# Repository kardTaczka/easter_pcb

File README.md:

# Easter PCB

## Quick view of PCB

Below are presented screenshots of 3d render PCB and schematic.

### 1. Front

### 2. Back

### 3. Schematic

---

## About
**Dual-Channel Alternating Output** -  The NE555 timer operates at approximately 0.2 Hz. Its square wave output is smoothed by an RC integration network consisting of a 10 kΩ resistor and a 50 µF capacitor bank (achieved by placing five 10 µF MLCCs in parallel). This analog signal drives a complementary transistor pair consisting of a BCP56 (NPN) and a BCP53 (PNP). 

Instead of driving a single array, the load is split into two separate LED rails. Because the NPN and PNP transistors conduct on opposite voltage swings, they create an alternating "breathing" effect. When the capacitor charges, the NPN rail fades in while the PNP rail fades out. When the voltage drops, the cycle reverses. The peak forward current is hardware-limited to a safe and visually pleasing 3 mA per LED.

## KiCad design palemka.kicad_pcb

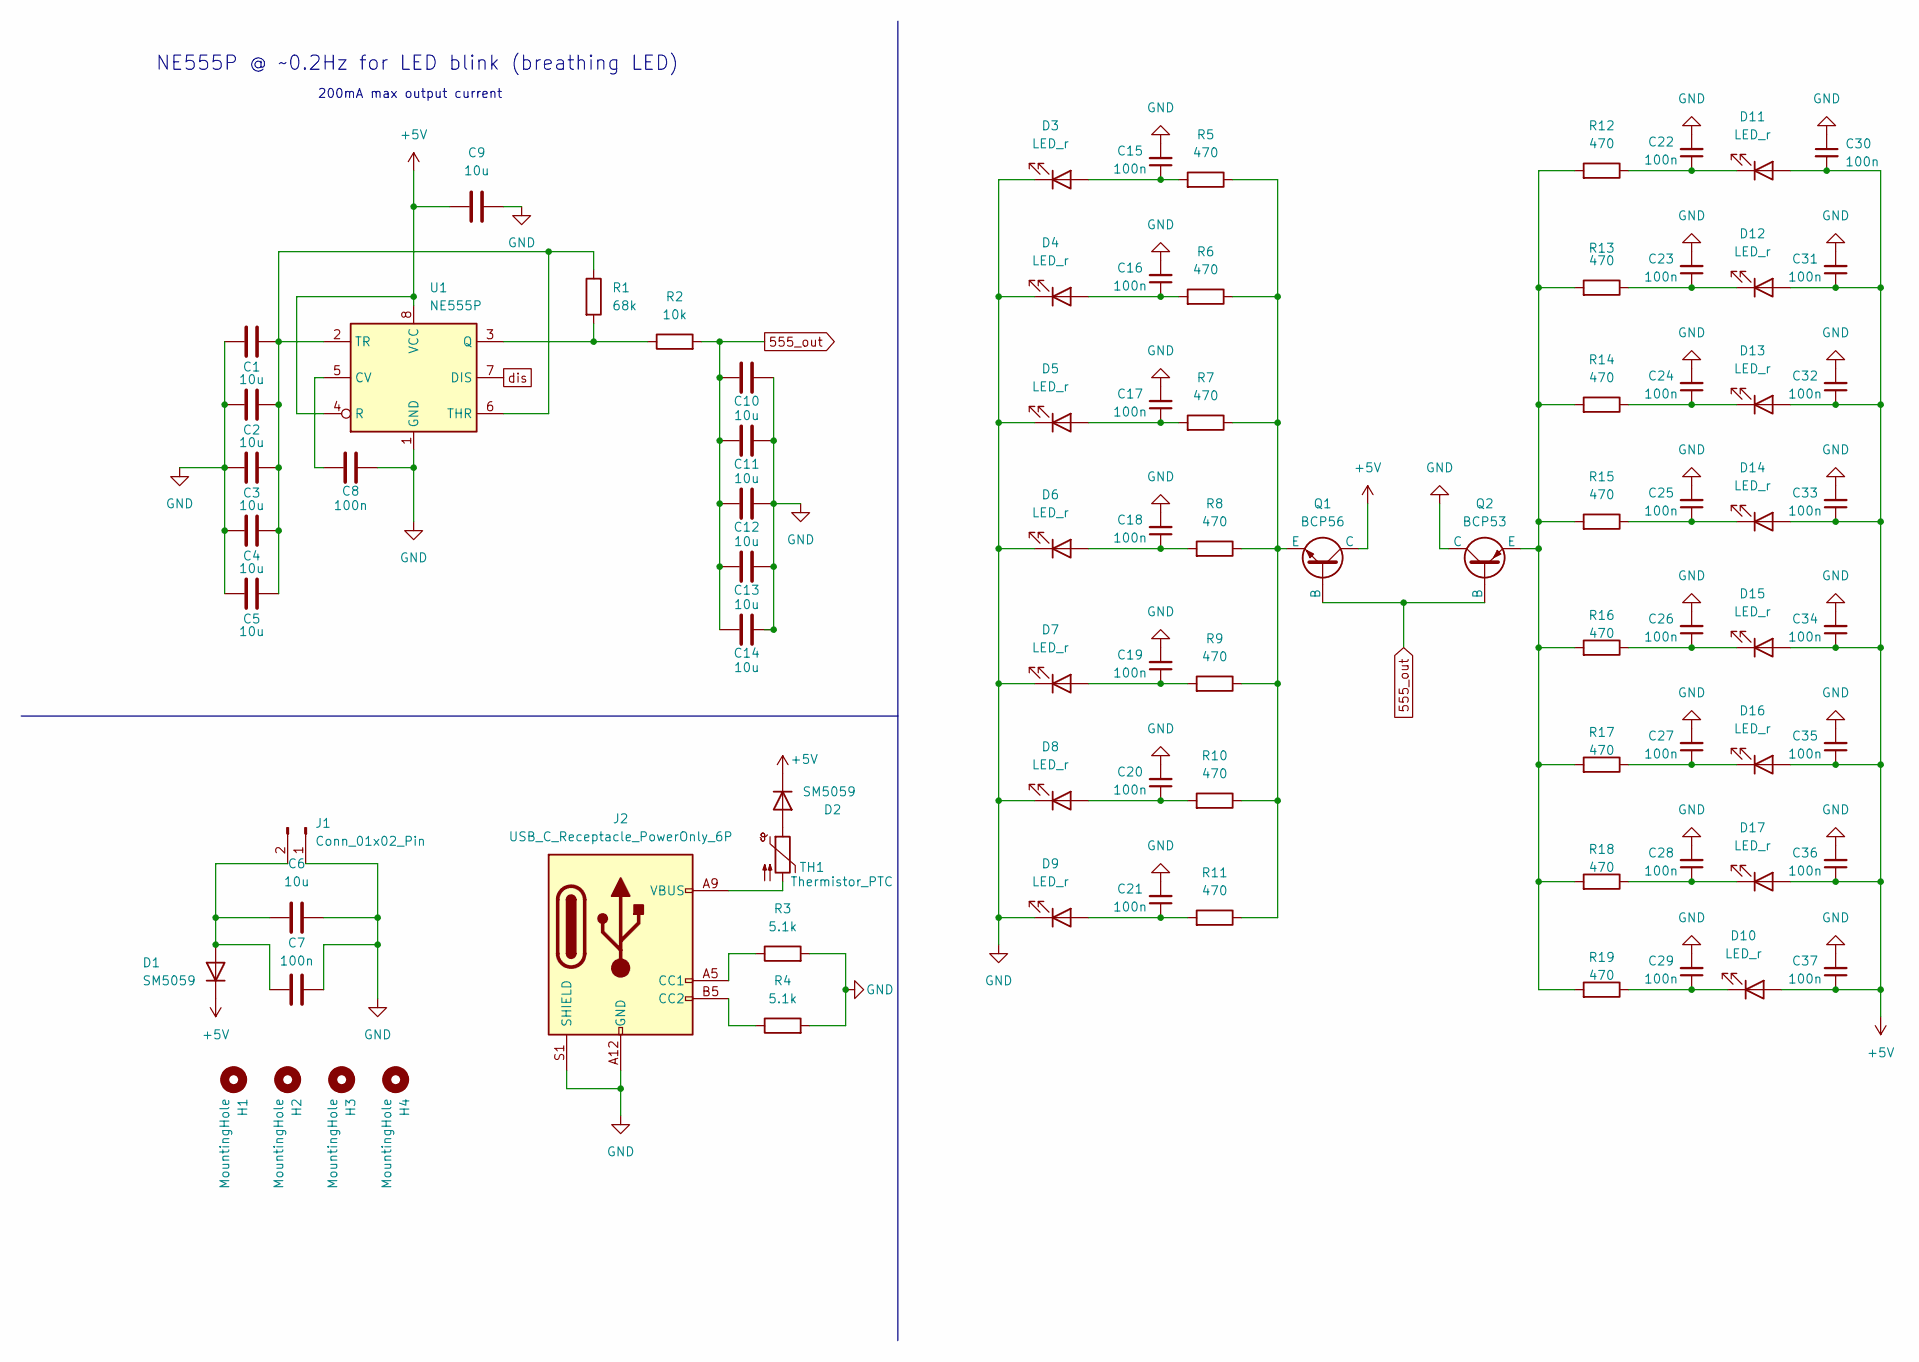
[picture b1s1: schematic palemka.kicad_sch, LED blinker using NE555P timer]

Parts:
C1, C2, C3, C4, C5, C6, C9, C10, C11, C12, C13, C14: 10u; C_0805_2012Metric_Pad1.18x1.45mm_HandSolder
C7, C8, C15, C16, C17, C18, C19, C20, C21, C22, C23, C24, C25, C26, C27, C28, C29, C30, C31, C32, C33, C34, C35, C36, C37: 100n; C_0805_2012Metric_Pad1.18x1.45mm_HandSolder
D1, D2: SM5059; D_SMA
D3, D4, D5, D6, D7, D8, D9, D10, D11, D12, D13, D14, D15, D16, D17: LED_r; LED_0805_2012Metric_Pad1.15x1.40mm_HandSolder
H1, H2, H3, H4: MountingHole; MountingHole_3.2mm_M3
J1: Conn_01x02_Pin; PinHeader_1x02_P2.54mm_Vertical
J2: USB_C_Receptacle_PowerOnly_6P; usb4970
Q1: BCP56; SOT-223
Q2: BCP53; SOT-223
R1: 68k; R_0805_2012Metric_Pad1.20x1.40mm_HandSolder
R2: 10k; R_0805_2012Metric_Pad1.20x1.40mm_HandSolder
R3, R4: 5.1k; R_0805_2012Metric_Pad1.20x1.40mm_HandSolder
R5, R6, R7, R8, R9, R10, R11, R12, R13, R14, R15, R16, R17, R18, R19: 470; R_0805_2012Metric_Pad1.20x1.40mm_HandSolder
TH1: Thermistor_PTC; R_1206_3216Metric_Pad1.30x1.75mm_HandSolder
U1: NE555P; SOIC-8_3.9x4.9mm_P1.27mm

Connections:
555_out: C10.1, C11.1, C12.1, C13.1, C14.1, Q1.2 (B), Q2.2 (B), R2.2
+5V: C9.1, C30.2, C31.1, C32.1, C33.1, C34.1, C35.1, C36.1, C37.1, D1.1 (K), D2.1 (K), D10.2 (A), D11.2 (A), D12.2 (A), D13.2 (A), D14.2 (A), D15.2 (A), D16.2 (A), D17.2 (A), Q1.1 (C), U1.4 (R), U1.8 (VCC)
GND: C1.2, C2.2, C3.2, C4.2, C5.2, C6.2, C7.1, C8.2, C9.2, C10.2, C11.2, C12.2, C13.2, C14.2, C15.2, C16.2, C17.2, C18.2, C19.2, C20.2, C21.2, C22.2, C23.2, C24.2, C25.2, C26.2, C27.2, C28.2, C29.2, C30.1, C31.2, C32.2, C33.2, C34.2, C35.2, C36.2, C37.2, D3.1 (K), D4.1 (K), D5.1 (K), D6.1 (K), D7.1 (K), D8.1 (K), D9.1 (K), J1.1, J2.A12 (GND), J2.B12 (GND), J2.S1 (SHIELD), Q2.1 (C), R3.2, R4.2, U1.1 (GND)
unnamed: C6.1, C7.2, D1.2 (A), J1.2
unnamed: D2.2 (A), TH1.1
unnamed: C15.1, D3.2 (A), R5.2
unnamed: C16.1, D4.2 (A), R6.2
unnamed: C17.1, D5.2 (A), R7.2
unnamed: C18.1, D6.2 (A), R8.2
unnamed: C19.1, D7.2 (A), R9.2
unnamed: C20.1, D8.2 (A), R10.2
unnamed: C21.1, D9.2 (A), R11.2
unnamed: C29.1, D10.1 (K), R19.1
unnamed: C22.1, D11.1 (K), R12.1
unnamed: C23.1, D12.1 (K), R13.1
unnamed: C24.1, D13.1 (K), R14.1
unnamed: C25.1, D14.1 (K), R15.1
unnamed: C26.1, D15.1 (K), R16.1
unnamed: C27.1, D16.1 (K), R17.1
unnamed: C28.1, D17.1 (K), R18.1
unnamed: J2.A5 (CC1), R3.1
unnamed: J2.B5 (CC2), R4.1
unnamed: J2.A9 (VBUS), J2.B9 (VBUS), TH1.2
unnamed: Q1.3 (E), R5.1, R6.1, R7.1, R8.1, R9.1, R10.1, R11.1
unnamed: Q2.3 (E), R12.2, R13.2, R14.2, R15.2, R16.2, R17.2, R18.2, R19.2
unnamed: C8.1, U1.5 (CV)
unnamed: R1.2, R2.1, U1.3 (Q)
unnamed: C1.1, C2.1, C3.1, C4.1, C5.1, R1.1, U1.2 (TR), U1.6 (THR)
dis: U1.7 (DIS)

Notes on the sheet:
NE555P @ ~0.2Hz for LED blink (breathing LED)
200mA max output current

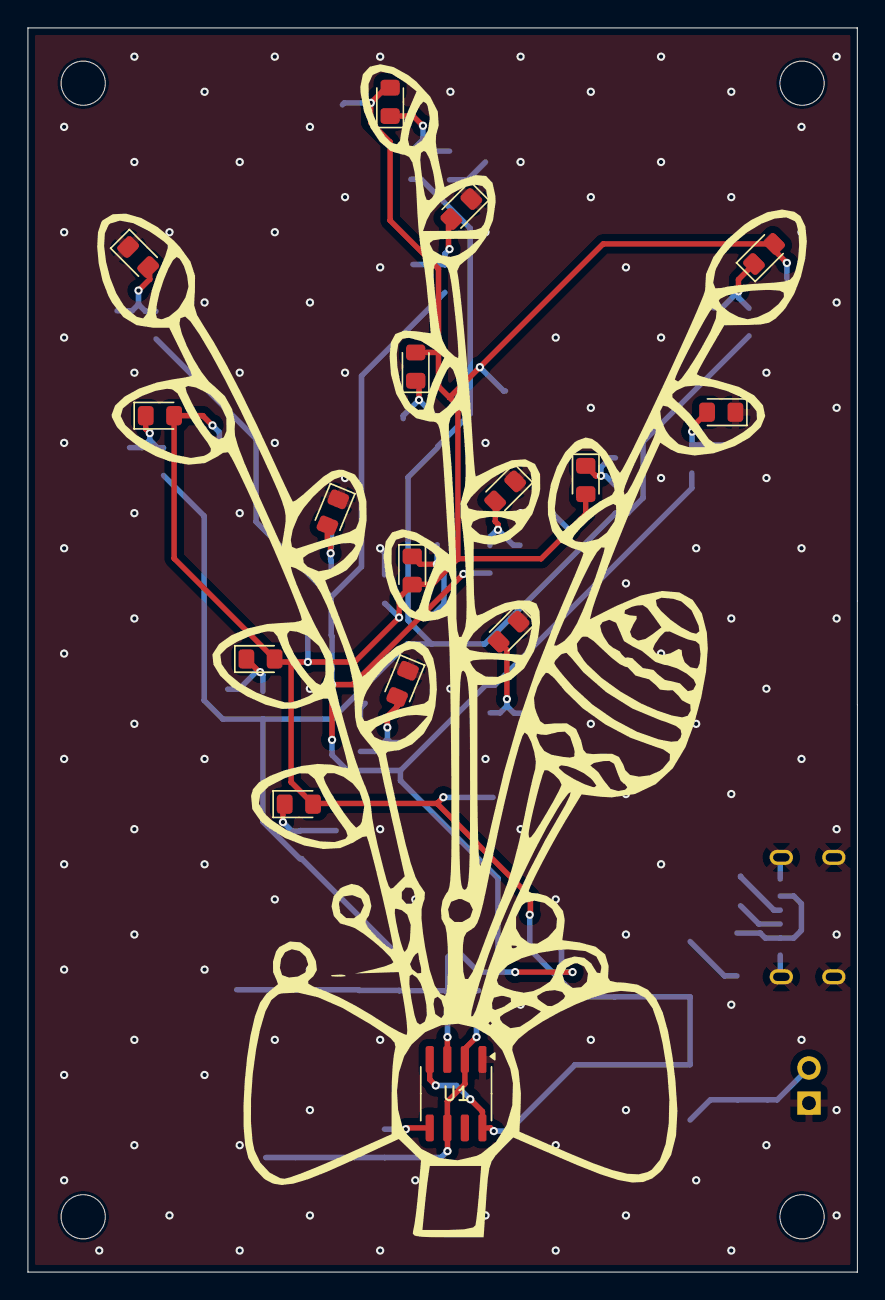
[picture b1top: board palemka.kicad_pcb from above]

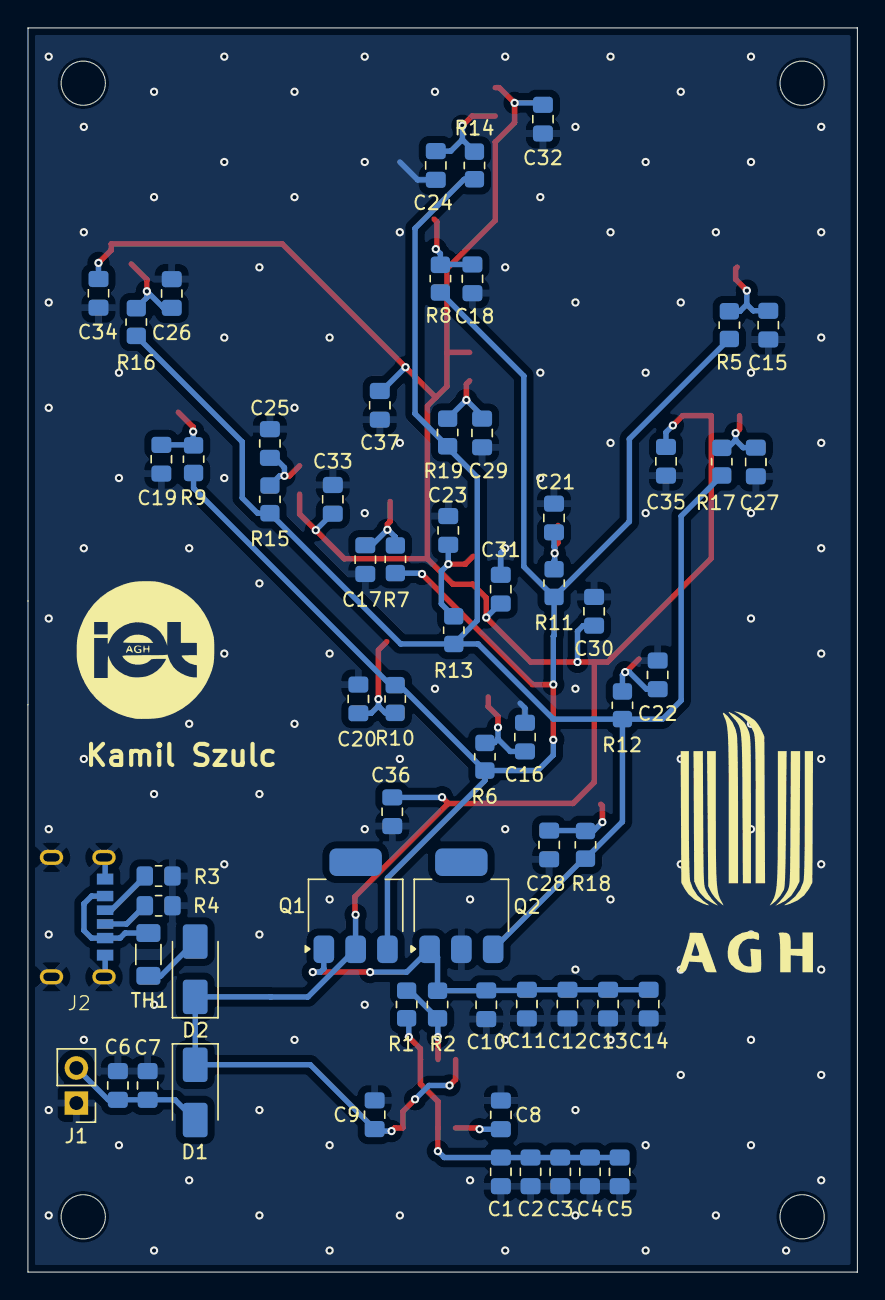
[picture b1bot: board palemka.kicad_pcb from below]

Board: 2 copper layers, 60.0 x 90.0 mm, 83 parts (63 on the bottom side), 28 nets.

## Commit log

2026-05-26 added photos
